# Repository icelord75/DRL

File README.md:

# DRL
Daytime Running Light controller

**DRL** is available under GPL License.

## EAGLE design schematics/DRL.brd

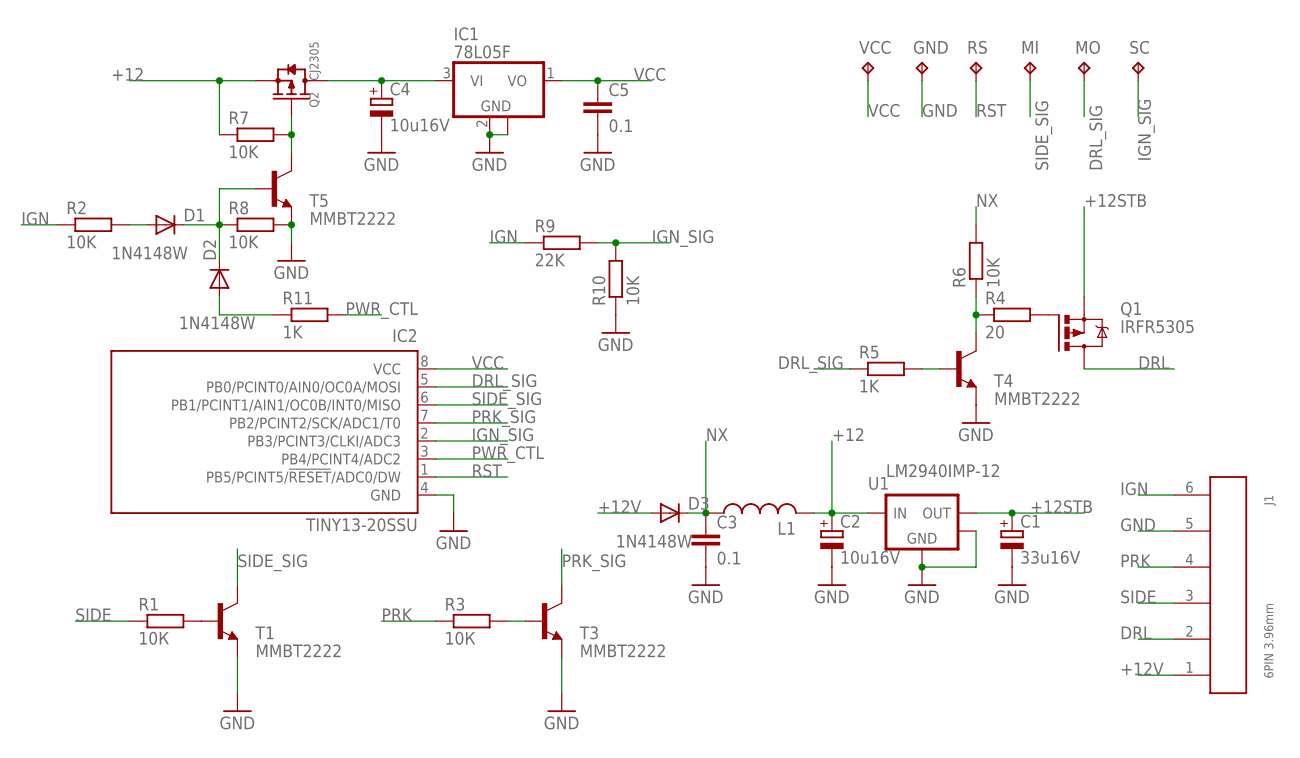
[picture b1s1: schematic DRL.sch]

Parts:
C1: 33u16V; SMC_B
C2, C4: 10u16V; SMC_B
C3, C5: 0.1; C0805
D1, D2, D3: 1N4148W; DO214AC
GND: TPB2,54; B2,54
IC1: 78L05F; SOT89
IC2: TINY13-20SSU; 8S1
J1: 6PIN 3.96mm; 645006114822
L1: L-USL5038P; L5038P
MI: TPB2,54; B2,54
MO: TPB2,54; B2,54
Q1: IRFR5305; D-PAK_TO252AA
Q2: CJ2305; SOT-23
R1, R3: 10К; R0805W
R2, R6, R7, R8, R10: 10K; R0805W
R4: 20; R0805W
R5, R11: 1K; R0805W
R9: 22K; R0805W
RS: TPB2,54; B2,54
SC: TPB2,54; B2,54
T1, T3, T4, T5: MMBT2222; SOT23-BEC
U1: LM2940IMP-12; SOT-223-3
VCC: TPB2,54; B2,54

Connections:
+12: C2.+, L1.2, Q2.2 (S), R7.1, U1.1 (VIN)
+12STB: C1.+, Q1.3 (S), U1.3 (VOUT)
+12V: D3.A, J1.1
DRL: J1.2, Q1.4 (D)
DRL_SIG: IC2.5 (PB0/PCINT0/AIN0/OC0A/MOSI), MO.TP, R5.1
GND: C1.-, C2.-, C3.2, C4.-, C5.2, GND.TP, IC1.2 (GND), IC1.2@1 (GND), IC2.4 (GND), J1.5, R8.2, R10.1, T1.E, T3.E, T4.E, T5.E, U1.2 (GND), U1.4 (TAB)
IGN: J1.6, R2.1, R9.1
IGN_SIG: IC2.2 (PB3/PCINT3/CLKI/ADC3), R9.2, R10.2, SC.TP
unnamed: R1.2, T1.B
unnamed: R3.2, T3.B
unnamed: D1.A, R2.2
unnamed: C4.+, IC1.3 (VI), Q2.3 (D)
unnamed: Q2.1 (G), R7.2, T5.C
unnamed: Q1.1 (G), R4.2
unnamed: D1.C, D2.C, R8.1, T5.B
unnamed: D2.A, R11.1
unnamed: R4.1, R6.1, T4.C
unnamed: R5.2, T4.B
NX: C3.1, D3.C, L1.1, R6.2
PRK: J1.4, R3.1
PRK_SIG: IC2.7 (PB2/PCINT2/SCK/ADC1/T0), T3.C
PWR_CTL: IC2.3 (PB4/PCINT4/ADC2), R11.2
RST: IC2.1 (PB5/PCINT5/!RESET!/ADC0/DW), RS.TP
SIDE: J1.3, R1.1
SIDE_SIG: IC2.6 (PB1/PCINT1/AIN1/OC0B/INT0/MISO), MI.TP, T1.C
VCC: C5.1, IC1.1 (VO), IC2.8 (VCC), VCC.TP

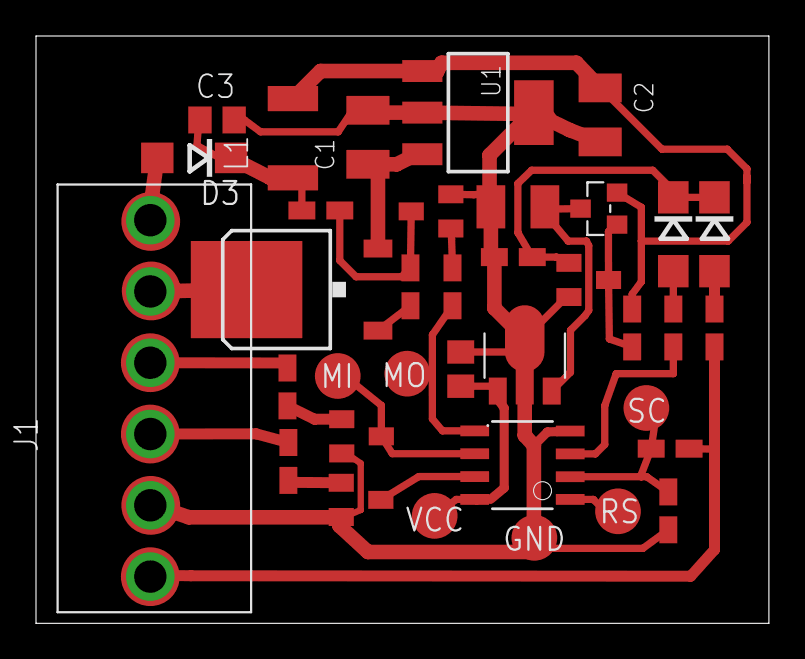
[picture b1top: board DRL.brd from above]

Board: 2 copper layers, 40.7 x 32.6 mm, 36 parts (0 on the bottom side), 26 nets.

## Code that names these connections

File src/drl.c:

/*
   //      _______ __  _________ _________
   //      \_     |  |/  .  \   |   \ ___/
   //        / :  |   \  /   \  |   / _>_
   //       /      \ | \ |   /  |  /     \
   //      /   |___/___/____/ \___/_     /
   //      \___/--------TECH--------\___/
   //        ==== ABOVE SINCE 1994 ====
   //
   //  Ab0VE TECH - DRivingLights Controller
   //
 */

#include <avr/io.h>
#include <avr/interrupt.h>
#include <util/delay.h>

// CONFIG
#define DRL_SIG   PINB0 // DRL output
#define SIDE_SIG  PINB1 // Sidemarkers
#define PRK_SIG   PINB2 // P/N AT selector
#define IGN_SIG   PINB3 // ADC - iginition prent
#define PWR_SIG   PINB4 // keep ON

#define FULL_DRL  255
#define DIM_DRL   128
#define FULL_DRL_ON_SHUTDOWN // switch on 100% DRL on SHUTDOWN

#define DELAY 1000
#define DELAY_SHUTDOWN 10000 // N times of DELAY

uint8_t DRL_ILLUMINACE=0;
uint8_t DRL_STATE=0;
int16_t DEAD_COUNTER=-1;
uint8_t counter=0;
uint8_t DRL_buf;

#define _SLEEP __asm__ __volatile__ ("sleep");

ISR (TIM0_OVF_vect) { //PWM via timer overflow
        if (++counter==0)
        {
                DRL_buf=DRL_STATE;
                PORTB |=_BV(DRL_SIG);
        }
        if (counter==DRL_buf) PORTB&=~_BV(DRL_SIG);
}

int main(){
        DDRB = _BV(DRL_SIG) | _BV(PWR_SIG);
        TIMSK0 = 0b00000010;
        TCCR0B = 0b00000001;
        sei();

        PORTB |= _BV(PWR_SIG); // latch POWER ON

        while (1) { // Main loop
// SIGNALS Reading
                if ((PORTB & _BV(SIDE_SIG))==0) { // No headlights
                        if ((PORTB & _BV(PRK_SIG))!=0) { // P or N position AT
                                DRL_ILLUMINACE=DIM_DRL; // 50%
                        } else
                                DRL_ILLUMINACE=FULL_DRL; // 100% on D
                } else
                        DRL_ILLUMINACE=0;

// IGNITION check
                if ((PORTB & _BV(IGN_SIG))==0) {         // IGNITION DOWN
                        DEAD_COUNTER=DELAY_SHUTDOWN; // Time-out before full OFF
#ifdef FULL_DRL_ON_SHUTDOWN
                        DRL_ILLUMINACE=255;
#endif
                } else
                {
                        if (DEAD_COUNTER>0) // restart ignition while shutdown
                        {
                                DEAD_COUNTER=-1; // stop shutdown
                        }
                }

// Dim or Bright controll
                if (DRL_ILLUMINACE>DRL_STATE) DRL_STATE++;
                if (DRL_ILLUMINACE<DRL_STATE) DRL_STATE--;

// Shutdown squence
                if (DEAD_COUNTER>0) DEAD_COUNTER--;
                if (DEAD_COUNTER==0) { // SHUTDOWN NOW
                        while (DRL_STATE > 0) {
                                DRL_STATE--;
                                _delay_us(DELAY);
                        }
                        PORTB = 0; // Clear DRL_SIG and PRW_SIG
                        _SLEEP; // If power not down for some reasons
                }

                _delay_us(DELAY);
        }
}

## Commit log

2017-10-17 Initial
2017-10-17 init
2017-10-17 scematics update

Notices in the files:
parts and their libraries:
Wurth_Elektronik_Electromechanic_Wire_to: Copyright: Würth Elektronik
